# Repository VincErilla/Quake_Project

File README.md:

# Quake_Project
All files/programs used in creating the quake sensors

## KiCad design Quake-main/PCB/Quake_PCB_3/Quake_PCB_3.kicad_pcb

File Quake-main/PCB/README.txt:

Quake_PCB_3 has the most recent pcb for the quake project, the production files are the versions that were ready to go to JLC PCB with 5 being the most recent that includes the rtc.

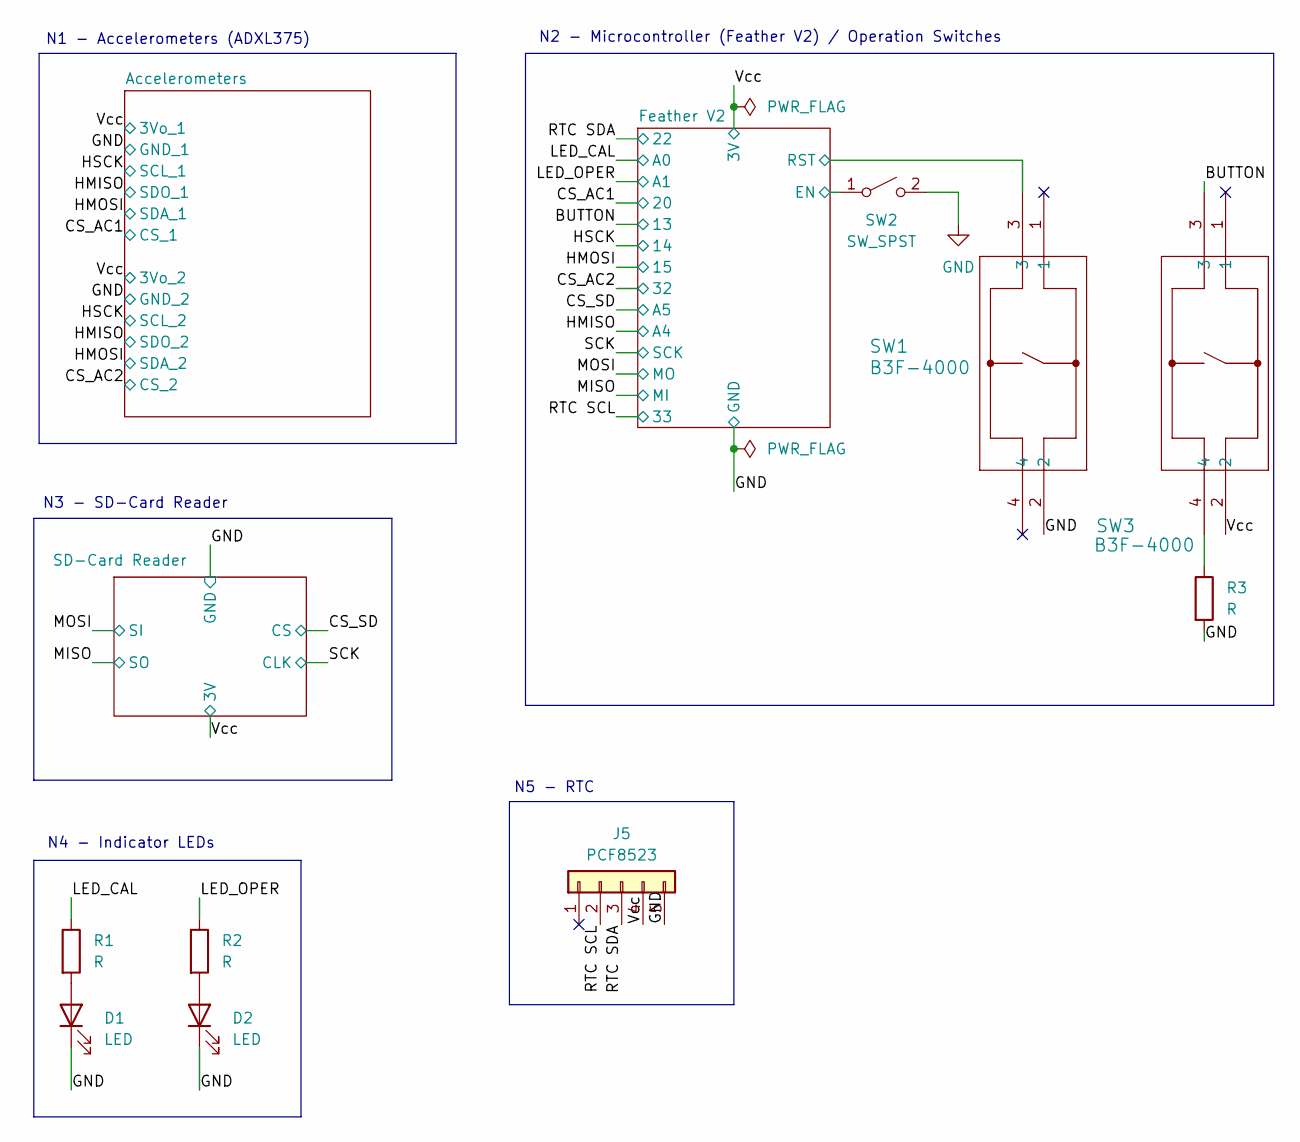
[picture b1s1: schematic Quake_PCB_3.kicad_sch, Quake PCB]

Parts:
D1, D2: LED; LED_D3.0mm
J5: PCF8523; PinHeader_1x05_P2.54mm_Vertical
R1, R2, R3: R; R_Axial_DIN0204_L3.6mm_D1.6mm_P7.62mm_Horizontal
SW1: B3F-4000; SW_B3F-4000_OMR
SW2: SW_SPST; PinHeader_1x02_P2.54mm_Vertical
SW3: B3F-4000; SW_SPST_Omron_B3F-40xx

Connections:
/BUTTON: SW3.3; also elsewhere on the board
/Feather V2/EN: SW2.1 (A); also elsewhere on the board
/Feather V2/RST: SW1.3; also elsewhere on the board
/LED_CAL: R1.1; also elsewhere on the board
/LED_OPER: R2.1; also elsewhere on the board
/RTC SCL: J5.2 (SCL); also elsewhere on the board
/RTC SDA: J5.3 (SDA); also elsewhere on the board
/Vcc: J5.4 (VCC), SW3.2; also elsewhere on the board
GND: D1.1 (K), D2.1 (K), J5.5 (GND), R3.2, SW1.2, SW2.2 (B); also elsewhere on the board
unnamed: D1.2 (A), R1.2
unnamed: D2.2 (A), R2.2
unnamed: R3.1, SW3.4

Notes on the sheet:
N4 - Indicator LEDs
N3 - SD-Card Reader
N5 - RTC
N1 - Accelerometers (ADXL375)
N2 - Microcontroller (Feather V2) / Operation Switches

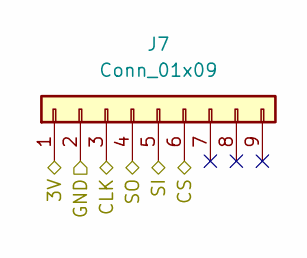
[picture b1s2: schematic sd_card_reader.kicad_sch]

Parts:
J7: Conn_01x09; PinHeader_1x09_P2.54mm_Vertical

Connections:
/CS_SD: J7.6; also elsewhere on the board
/MISO: J7.4; also elsewhere on the board
/MOSI: J7.5; also elsewhere on the board
/SCK: J7.3; also elsewhere on the board
/Vcc: J7.1; also elsewhere on the board
GND: J7.2; also elsewhere on the board

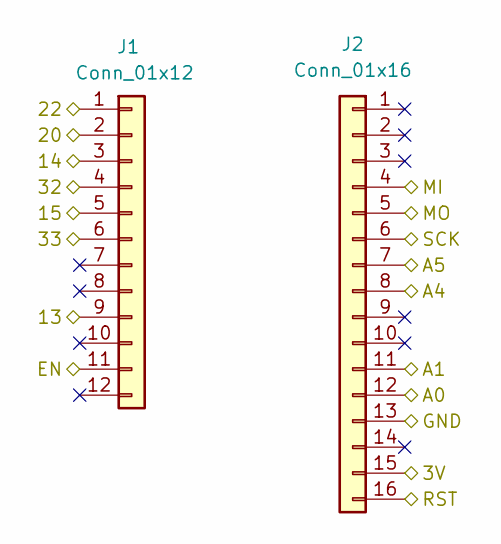
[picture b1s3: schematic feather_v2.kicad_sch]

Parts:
J1: Conn_01x12; PinHeader_1x12_P2.54mm_Vertical
J2: Conn_01x16; PinHeader_1x16_P2.54mm_Vertical

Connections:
/BUTTON: J1.9; also elsewhere on the board
/CS_AC1: J1.2; also elsewhere on the board
/CS_AC2: J1.4; also elsewhere on the board
/CS_SD: J2.7; also elsewhere on the board
/Feather V2/EN: J1.11; also elsewhere on the board
/Feather V2/RST: J2.16; also elsewhere on the board
/HMISO: J2.8; also elsewhere on the board
/HMOSI: J1.5; also elsewhere on the board
/HSCK: J1.3; also elsewhere on the board
/LED_CAL: J2.12; also elsewhere on the board
/LED_OPER: J2.11; also elsewhere on the board
/MISO: J2.4; also elsewhere on the board
/MOSI: J2.5; also elsewhere on the board
/RTC SCL: J1.6; also elsewhere on the board
/RTC SDA: J1.1; also elsewhere on the board
/SCK: J2.6; also elsewhere on the board
/Vcc: J2.15; also elsewhere on the board
GND: J2.13; also elsewhere on the board

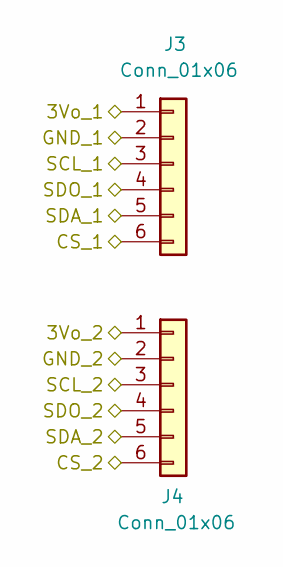
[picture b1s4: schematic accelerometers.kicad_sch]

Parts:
J3, J4: Conn_01x06; PinHeader_2x03_P2.54mm_Vertical

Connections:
/CS_AC1: J3.6; also elsewhere on the board
/CS_AC2: J4.6; also elsewhere on the board
/HMISO: J3.4, J4.4; also elsewhere on the board
/HMOSI: J3.5, J4.5; also elsewhere on the board
/HSCK: J3.3, J4.3; also elsewhere on the board
/Vcc: J3.1, J4.1; also elsewhere on the board
GND: J3.2, J4.2; also elsewhere on the board

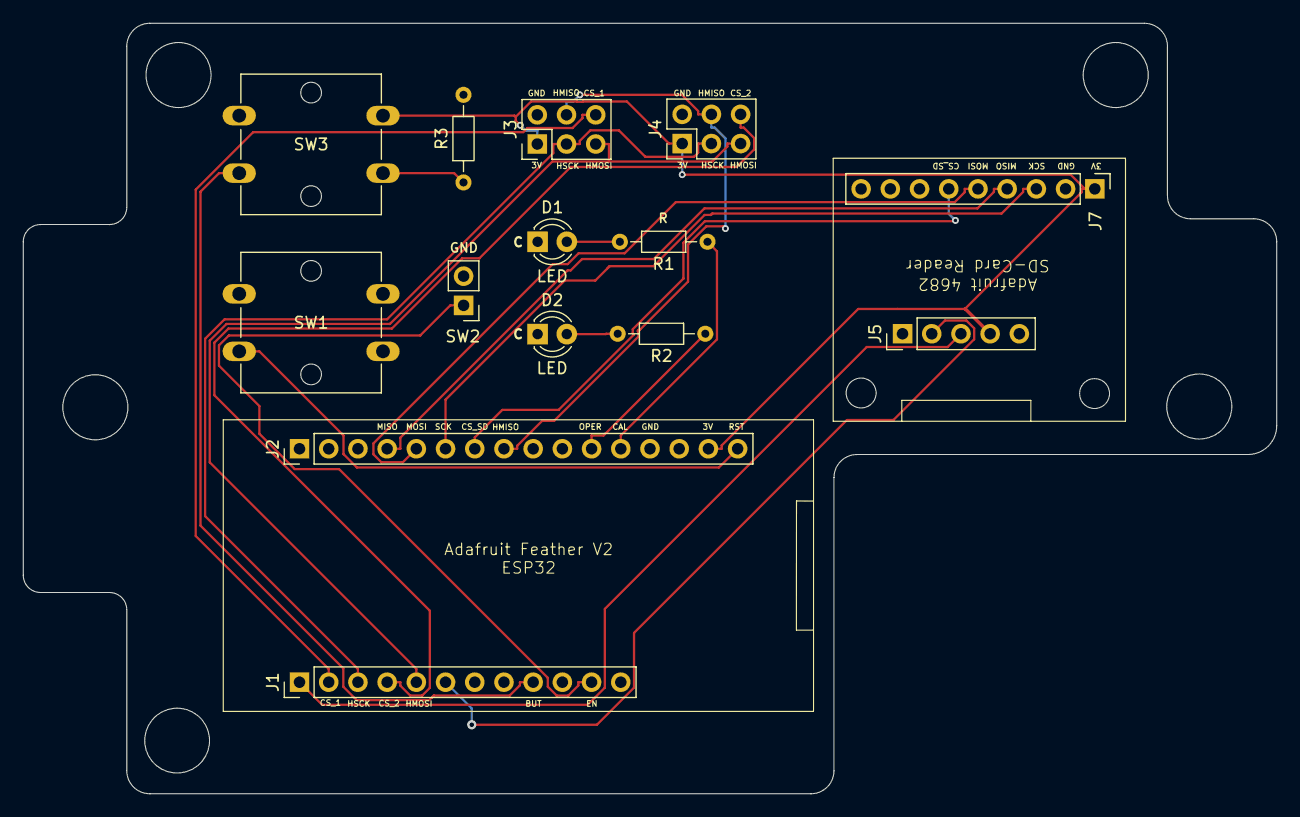
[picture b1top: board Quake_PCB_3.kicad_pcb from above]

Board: 2 copper layers, 109.0 x 67.0 mm, 14 parts (0 on the bottom side), 21 nets.

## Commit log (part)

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2026-06-08 Most recent Files/Changes
2026-06-08 added Real-Time Mag. code
2026-06-10 changed the vibe7 and MATLAB code to have working RTC and handling random zeroes appearing after installing shielding
2026-06-11 Changed a few things to acomodate another shielded cable. Flippin Brutal Burh
2026-06-16 Added logic block to print which Accelerometer is failing
2026-06-23 Changed the Vibe7 code to fit 2 accelerometers per ethernet. Will remove due to change of plans
